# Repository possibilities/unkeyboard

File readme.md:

# Unkeyboard

Unkeyboard is a set of python scripts, using [CadQuery](https://cadquery.readthedocs.io/), for generating stacked acrylic cases for [Atreus](https://github.com/profet23/atreus62)-style keyboards. The case is derived from the [62 key case](https://github.com/profet23/atreus62) but generating similar cases for the [42 key](https://atreus.technomancy.us/) and [44 key](https://shop.keyboard.io/products/keyboardio-atreus) variations is also supported. By default a [Chicago bolt](https://en.wikipedia.org/wiki/Sex_bolt) is used, a wider bezel is added around the keys, and sharp corners replace the curved corners of the original. Generated cases can be [hand wired](https://beta.docs.qmk.fm/using-qmk/guides/keyboard-building/hand_wire) or used with [available PCBs](https://shop.profetkeyboards.com/product/atreus62-pcb).

## Development

PCB rendering will take a very long time and lock up CQ-Editor unless you lower the rendering tolerance.

* Open: `Preferences -> 3D Viewer -> Deviation`
* Value: `0.001`

## Credits

* Initial case and PCB dimensions are reverse engineered from the [Atreus64 project](https://github.com/profet23/atreus62).
* Switch footprint from Dale Price's [Keyswitches library](https://github.com/daprice/keyswitches.pretty)
* Diode and Pro Micro footprint from Kosuke Adachi's [KBD library](https://github.com/foostan/kbd)

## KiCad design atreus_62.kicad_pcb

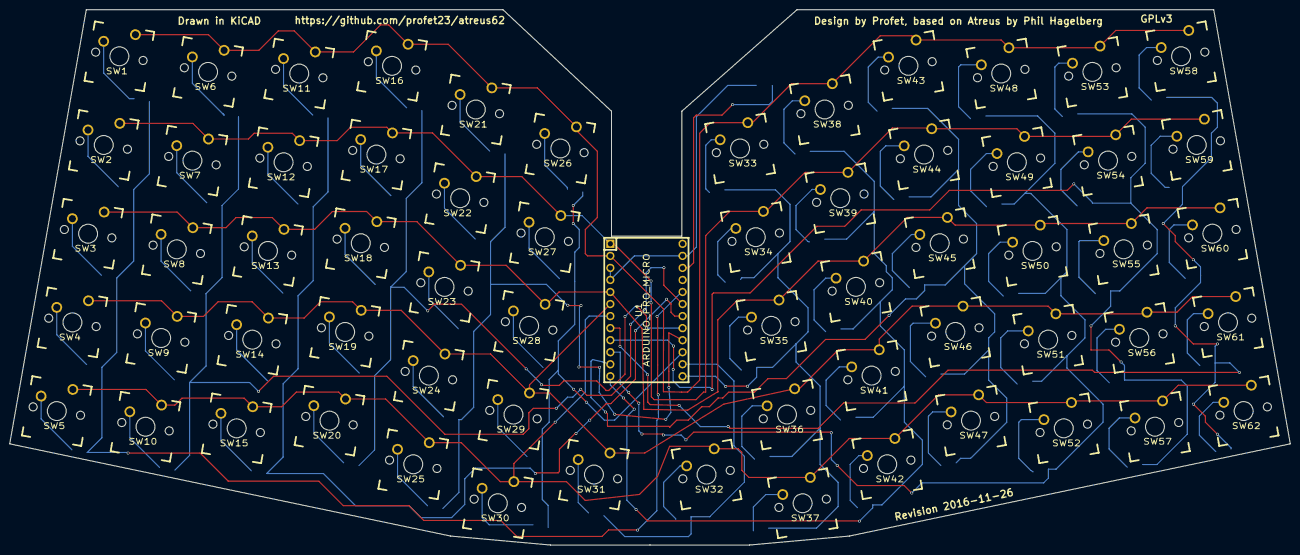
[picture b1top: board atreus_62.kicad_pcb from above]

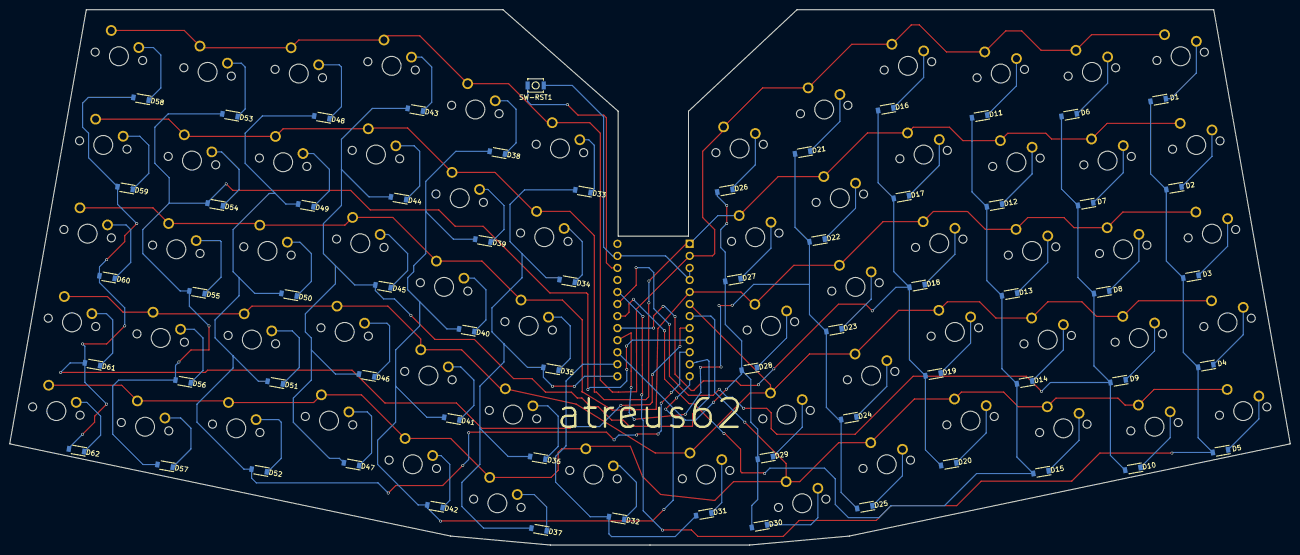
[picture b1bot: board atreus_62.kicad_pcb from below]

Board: 2 copper layers, 270.1 x 112.9 mm, 126 parts (62 on the bottom side), 82 nets.

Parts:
D1, D2, D3, D4, D5, D6, D7, D8, D9, D10, D11, D12, D13, D14, D15, D16, D17, D18, D19, D20, D21, D22, D23, D24, D25, D26, D27, D28, D29, D30, D31, D32, D33, D34, D35, D36, D37, D38, D39, D40, D41, D42, D43, D44, D45, D46, D47, D48, D49, D50, D51, D52, D53, D54, D55, D56, D57, D58, D59, D60, D61, D62: DIODE; SOD-123
SW1, SW2, SW3, SW4, SW5, SW6, SW7, SW8, SW9, SW10, SW11, SW12, SW13, SW14, SW15, SW16, SW17, SW18, SW19, SW20, SW21, SW22, SW23, SW24, SW25, SW26, SW27, SW28, SW29, SW30, SW31, SW32, SW33, SW34, SW35, SW36, SW37, SW38, SW39, SW40, SW41, SW42, SW43, SW44, SW45, SW46, SW47, SW48, SW49, SW50, SW51, SW52, SW53, SW54, SW55, SW56, SW57, SW58, SW59, SW60, SW61, SW62: SWITCH_PUSH; CHERRY_PCB_100H
SW-RST1: SWITCH_PUSH; SW_SPST_B3U-1000P
U1: ARDUINO_PRO_MICRO

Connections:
/COL0: D1.2, D2.2, D3.2, D4.2, D5.2, U1.20
/COL1: D6.2, D7.2, D8.2, D9.2, D10.2, U1.19
/COL2: D11.2, D12.2, D13.2, D14.2, D15.2, U1.18
/COL3: D16.2, D17.2, D18.2, D19.2, D20.2, U1.17
/COL4: D21.2, D22.2, D23.2, D24.2, D25.2, U1.16
/COL5: D26.2, D27.2, D28.2, D29.2, D30.2, U1.15
/COL6: D31.2, D32.2, U1.14
/COL7: D33.2, D34.2, D35.2, D36.2, D37.2, U1.13
/COL8: D38.2, D39.2, D40.2, D41.2, D42.2, U1.12
/COL9: D43.2, D44.2, D45.2, D46.2, D47.2, U1.11
/COL10: D48.2, D49.2, D50.2, D51.2, D52.2, U1.10
/COL11: D53.2, D54.2, D55.2, D56.2, D57.2, U1.9
/COL12: D58.2, D59.2, D60.2, D61.2, D62.2, U1.8
/ROW0: SW5.1, SW10.1, SW15.1, SW20.1, SW25.1, SW30.1, SW32.1, SW37.1, SW42.1, SW47.1, SW52.1, SW57.1, SW62.1, U1.7
/ROW1: SW4.1, SW9.1, SW14.1, SW19.1, SW24.1, SW29.1, SW31.1, SW36.1, SW41.1, SW46.1, SW51.1, SW56.1, SW61.1, U1.6
/ROW2: SW3.1, SW8.1, SW13.1, SW18.1, SW23.1, SW28.1, SW35.1, SW40.1, SW45.1, SW50.1, SW55.1, SW60.1, U1.5
/ROW3: SW2.1, SW7.1, SW12.1, SW17.1, SW22.1, SW27.1, SW34.1, SW39.1, SW44.1, SW49.1, SW54.1, SW59.1, U1.1
/ROW4: SW1.1, SW6.1, SW11.1, SW16.1, SW21.1, SW26.1, SW33.1, SW38.1, SW43.1, SW48.1, SW53.1, SW58.1, U1.2
GND: SW-RST1.1, U1.3, U1.4, U1.23
unnamed: D1.1, SW1.2
unnamed: D2.1, SW2.2
unnamed: D3.1, SW3.2
unnamed: D4.1, SW4.2
unnamed: D5.1, SW5.2
unnamed: D6.1, SW6.2
unnamed: D7.1, SW7.2
unnamed: D8.1, SW8.2
unnamed: D9.1, SW9.2
unnamed: D10.1, SW10.2
unnamed: D11.1, SW11.2
unnamed: D12.1, SW12.2
unnamed: D13.1, SW13.2
unnamed: D14.1, SW14.2
unnamed: D15.1, SW15.2
unnamed: D16.1, SW16.2
unnamed: D17.1, SW17.2
unnamed: D18.1, SW18.2
unnamed: D19.1, SW19.2
unnamed: D20.1, SW20.2
unnamed: D21.1, SW21.2
unnamed: D22.1, SW22.2
unnamed: D23.1, SW23.2
unnamed: D24.1, SW24.2
unnamed: D25.1, SW25.2
unnamed: D26.1, SW26.2
unnamed: D27.1, SW27.2
unnamed: D28.1, SW28.2
unnamed: D29.1, SW29.2
unnamed: D30.1, SW30.2
unnamed: D31.1, SW31.2
unnamed: D32.1, SW32.2
unnamed: D33.1, SW33.2
unnamed: D34.1, SW34.2
unnamed: D35.1, SW35.2
unnamed: D36.1, SW36.2
unnamed: D37.1, SW37.2
unnamed: D38.1, SW38.2
unnamed: D39.1, SW39.2
unnamed: D40.1, SW40.2
unnamed: D41.1, SW41.2
unnamed: D42.1, SW42.2
unnamed: D43.1, SW43.2
unnamed: D44.1, SW44.2
unnamed: D45.1, SW45.2
unnamed: D46.1, SW46.2
unnamed: D47.1, SW47.2
unnamed: D48.1, SW48.2
unnamed: D49.1, SW49.2
unnamed: D50.1, SW50.2
unnamed: D51.1, SW51.2
unnamed: D52.1, SW52.2
unnamed: D53.1, SW53.2
unnamed: D54.1, SW54.2
unnamed: D55.1, SW55.2
unnamed: D56.1, SW56.2
unnamed: D57.1, SW57.2
unnamed: D58.1, SW58.2
unnamed: D59.1, SW59.2
unnamed: D60.1, SW60.2
unnamed: D61.1, SW61.2
unnamed: D62.1, SW62.2
unnamed: SW-RST1.2, U1.22

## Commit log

2021-09-26 Initial
2021-09-26 Move switch holes to code
2021-09-26 Cleanup
2021-09-28 Move dynamic wiring out of drawing
2021-10-08 CadQuery
2021-10-08 Improve model and code
2021-10-10 Drill holes and misc
2021-10-11 Clean out bezel and holes
2021-10-11 Cleanup and parameterize stagger
2021-10-14 Refactoring towards case
2021-10-18 Evolving concept
2021-10-18 Cleanup approach to drilling holes
2021-10-18 Add screw radius to config
2021-10-19 Cut hotsocket cutout blind from bottom
2021-10-30 Descope to Atreus only acrylic case
2021-10-30 Fix gitignore
2021-10-30 Export front faces only
2021-10-30 Cleanup export
2021-10-30 Preping for two inner keys
2021-10-30 Initial pass at SVG output
2021-10-30 Rename vars for clarity
2021-10-30 Continue working towards two inner keys
2021-10-30 Simplify export
2021-10-30 Improve explode
2021-10-30 Improve readme
2021-10-30 Get thickness by measuring
2021-10-30 Move explode to module and cleanup
2021-10-30 Bring back centering to avoid breaking layout
2021-10-30 Move var
2021-10-30 More cleanup
2021-10-30 Add flattening
2021-10-31 Separate export script
2021-10-31 Reorder vars
2021-10-31 Add snapshot test
2021-10-31 Rename before refactor
2021-10-31 Fix issues with bottom position
2021-10-31 Remove snapshots
2021-10-31 Add comment
2021-10-31 Add timings
2021-10-31 Renaming
2021-10-31 Add var for magic number
2021-10-31 Move fns around
2021-10-31 Use title case
2021-10-31 Calculate coords up front
2021-10-31 Misc cleanup
2021-11-01 Improve export
2021-11-01 Remove output
2021-11-02 Cleanup and renaming
2021-11-02 Feed config to make_keyboard_parts
2021-11-02 Allow config overrides
2021-11-02 Return geometry and inner switch plate together
2021-11-02 Rename
2021-11-02 Snapshot tests
2021-11-02 Remove view config obj
2021-11-02 Use pytest and syrupy
2021-11-02 Visual snapshot tests
2021-11-02 Change to GPL license
    This is needed because there is work derived from
    https://github.com/profet23/atreus62
2021-11-02 Fix test name
2021-11-04 Calculate geometry up front
2021-11-05 Add environment file
2021-11-05 Update view defaults
2021-11-05 Collapse pointfinding logic
2021-11-05 Cleanup switch cutouts
2021-11-05 Separate function for switch outline points
2021-11-05 Separate function for case outer points
2021-11-05 Separate function for spacer points
2021-11-05 Sep function for screw points
2021-11-05 Use moveTo for single point
2021-11-05 Move presets out of keyboard.py
2021-11-05 Prevent missing tests
2021-11-05 Pull out vars
2021-11-05 Better 2d array population
2021-11-05 Move reset info to geometry
2021-11-05 Cleanup geometry and avoid passing config
2021-11-05 Use alternate simple namespace syntax
2021-11-05 Remove environment
2021-11-05 Cleanup tests
2021-11-06 Add export-stl
2021-11-06 Rename and cleanup
2021-11-06 Separate modules for many files
2021-11-06 Rename fn
2021-11-06 Rename key to switch
2021-11-06 Remove timer
2021-11-07 Update name for consistency
2021-11-13 Update names
2021-11-15 Fix issue with fixture
    When generated the width of USB opening was 3 rather than 4
2021-11-15 Mirror points in 2d
2021-11-15 Remove unused
2021-11-19 Pcb experiment
2021-11-19 Flip everything over y axis to match kicad
2021-11-19 Fix rotation and drill holes
2021-11-19 Render pads
2021-11-19 Fix mode of many files
2021-11-20 Improve pads and cleanup
2021-11-21 Show segments
2021-11-21 Add silkscreens
2021-11-21 Cleanup and flatten structure
2021-11-21 Add var for yellow color
2021-11-21 Show pcb and case together
2021-11-21 Emit geometry when making case
2021-11-21 Fix export
2021-11-21 Show PCB and together
2021-11-21 Better centering of PCB
2021-11-21 Better PCB position
2021-11-21 Update names and fixtures
2021-11-21 Move calculation to fn
2021-11-21 Add empty PCB
2021-11-21 Move fn to module
2021-11-22 Fix variable placement
2021-11-22 Make pcb outline
2021-11-22 Create board data from geometry
2021-11-23 Use correct name in blank file
2021-11-24 Cleanup and render blank PCB
2021-11-24 Remove unecessary index
2021-11-24 Ensure nets is list
2021-11-24 Ensure footprints and skip when empty
2021-11-24 Ensure vias and skip when empty
2021-11-24 Ensure segments and skip when empty
2021-11-24 Ensure footprint defaults
2021-11-24 Simplify pcb parsing
2021-11-24 Rename attr
2021-11-27 Add cherry switch from kbd repo
2021-11-27 Fix hole drilling on blank pcb
2021-11-27 Upgrade footprint version
2021-11-27 Delint
2021-11-27 Configure flake8
2021-11-27 Fix config
2021-11-27 Cleanup config
2021-11-27 Start weening off named_points
2021-11-27 Continue moving away from named_points
2021-11-28 Fully get rid of named_points
2021-11-28 Remove pcb calculation from case geometry
2021-11-28 Rename keyboard to case
2021-11-28 Normalize naming
2021-11-28 Remove blank pcb files/logic
2021-11-28 Remove unused fn
2021-11-28 Cleanup and separate pcb geometry
2021-11-28 Avoid duplicate tests
2021-11-28 Remove remove dir when creating fixtures
2021-11-28 Simplify
2021-11-28 Split rotation of key positions into separate fn
2021-11-28 Cleanup and use non hotswap switch
2021-11-28 Fix PCB issues
2021-11-28 Use angles from config
2021-11-28 Flip pcb points over y axis
2021-11-29 WIP Rewrite PCB render
2021-11-29 Rewrite PCB render and cleanup
2021-11-29 Add diodes
2021-11-30 Use create_footprint
2021-11-30 Flip diodes
2021-12-01 Remove SimpleNamespace usage
2021-12-01 Rename fn/vars
2021-12-01 Separate function for pcb outline
2021-12-05 Fix rotation logic
2021-12-05 Allow fuse_parts to work with non solids
2022-01-23 Generate PCB

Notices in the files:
atreus_62.kicad_pcb:
GPLv3
